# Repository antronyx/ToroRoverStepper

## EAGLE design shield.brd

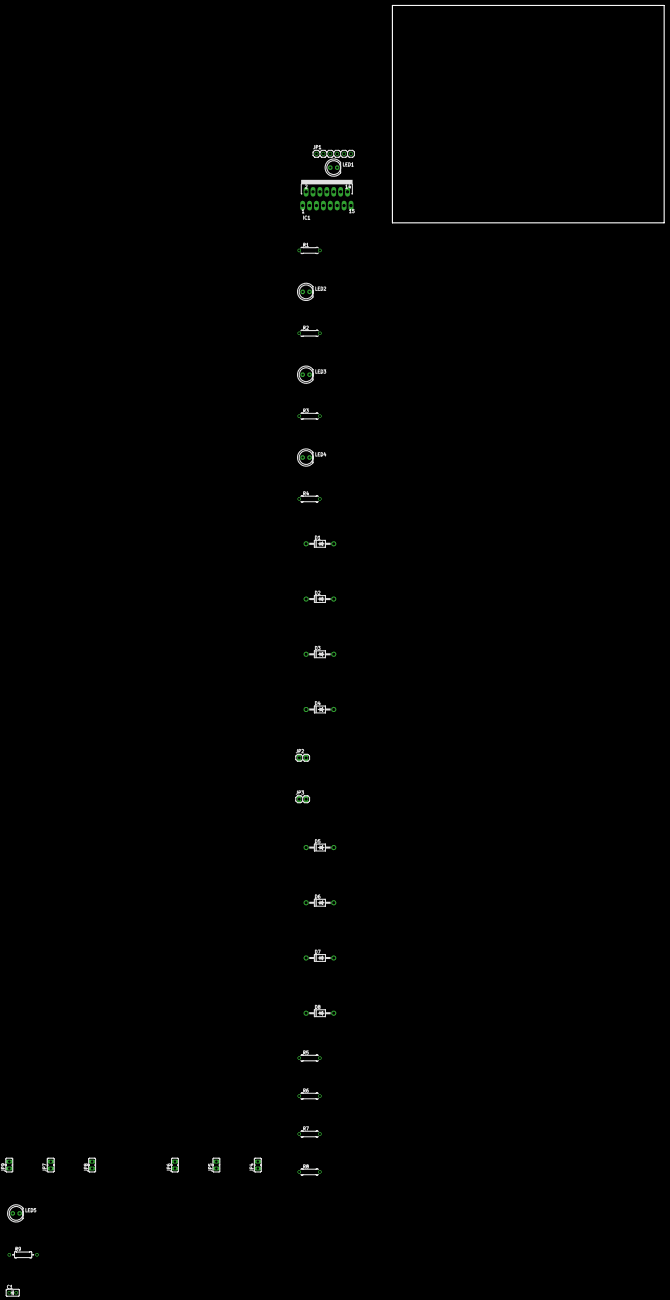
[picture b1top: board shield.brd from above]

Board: 2 copper layers, 100.0 x 80.0 mm, 33 parts (0 on the bottom side), 25 nets, no tracks yet.

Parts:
C1: C025-025X050
D1, D2, D3, D4, D5, D6, D7, D8: 1N4004; DO41-10
IC1: L298; MULTIWATT-15
JP1: 1X06
JP2, JP3: 1X02
JP4, JP5, JP6, JP7, JP8, JP9: JP1
LED1, LED2, LED3, LED4, LED5: LED5MM
R1, R2, R3, R4, R5, R6, R7, R8: 0207/7
R9: 0207/10

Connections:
+12V: D5.C, D6.C, D7.C, IC1.4
GND: D1.A, D2.A, D3.A, D4.A, IC1.8, JP7.2, JP9.2, R1.1
unnamed: IC1.6, JP1.6
unnamed: IC1.5, JP1.5, LED4.A, R8.1
unnamed: IC1.7, JP1.4, LED3.A, R7.1
unnamed: IC1.10, JP1.3, LED2.A, R6.1
unnamed: IC1.12, JP1.2, LED1.A, R5.1
unnamed: IC1.11, JP1.1
unnamed: LED1.K, R1.2
unnamed: LED2.K, R2.2
unnamed: LED3.K, R3.2
unnamed: LED4.K, R4.2
unnamed: D4.C, D8.A, IC1.14, JP2.2
unnamed: D3.C, D7.A, IC1.13, JP2.1
unnamed: D2.C, D6.A, IC1.3, JP3.2
unnamed: D1.C, D5.A, IC1.2, JP3.1
unnamed: JP4.1, R5.2
unnamed: JP5.1, R6.2
unnamed: JP6.1, R7.2
unnamed: JP8.1, R8.2
unnamed: IC1.1, JP7.1
unnamed: IC1.15, JP9.1
unnamed: LED5.K, R9.2
unnamed: C1.2, R9.1
VCC: IC1.9, JP4.2, JP5.2, JP6.2, JP8.2, LED5.A

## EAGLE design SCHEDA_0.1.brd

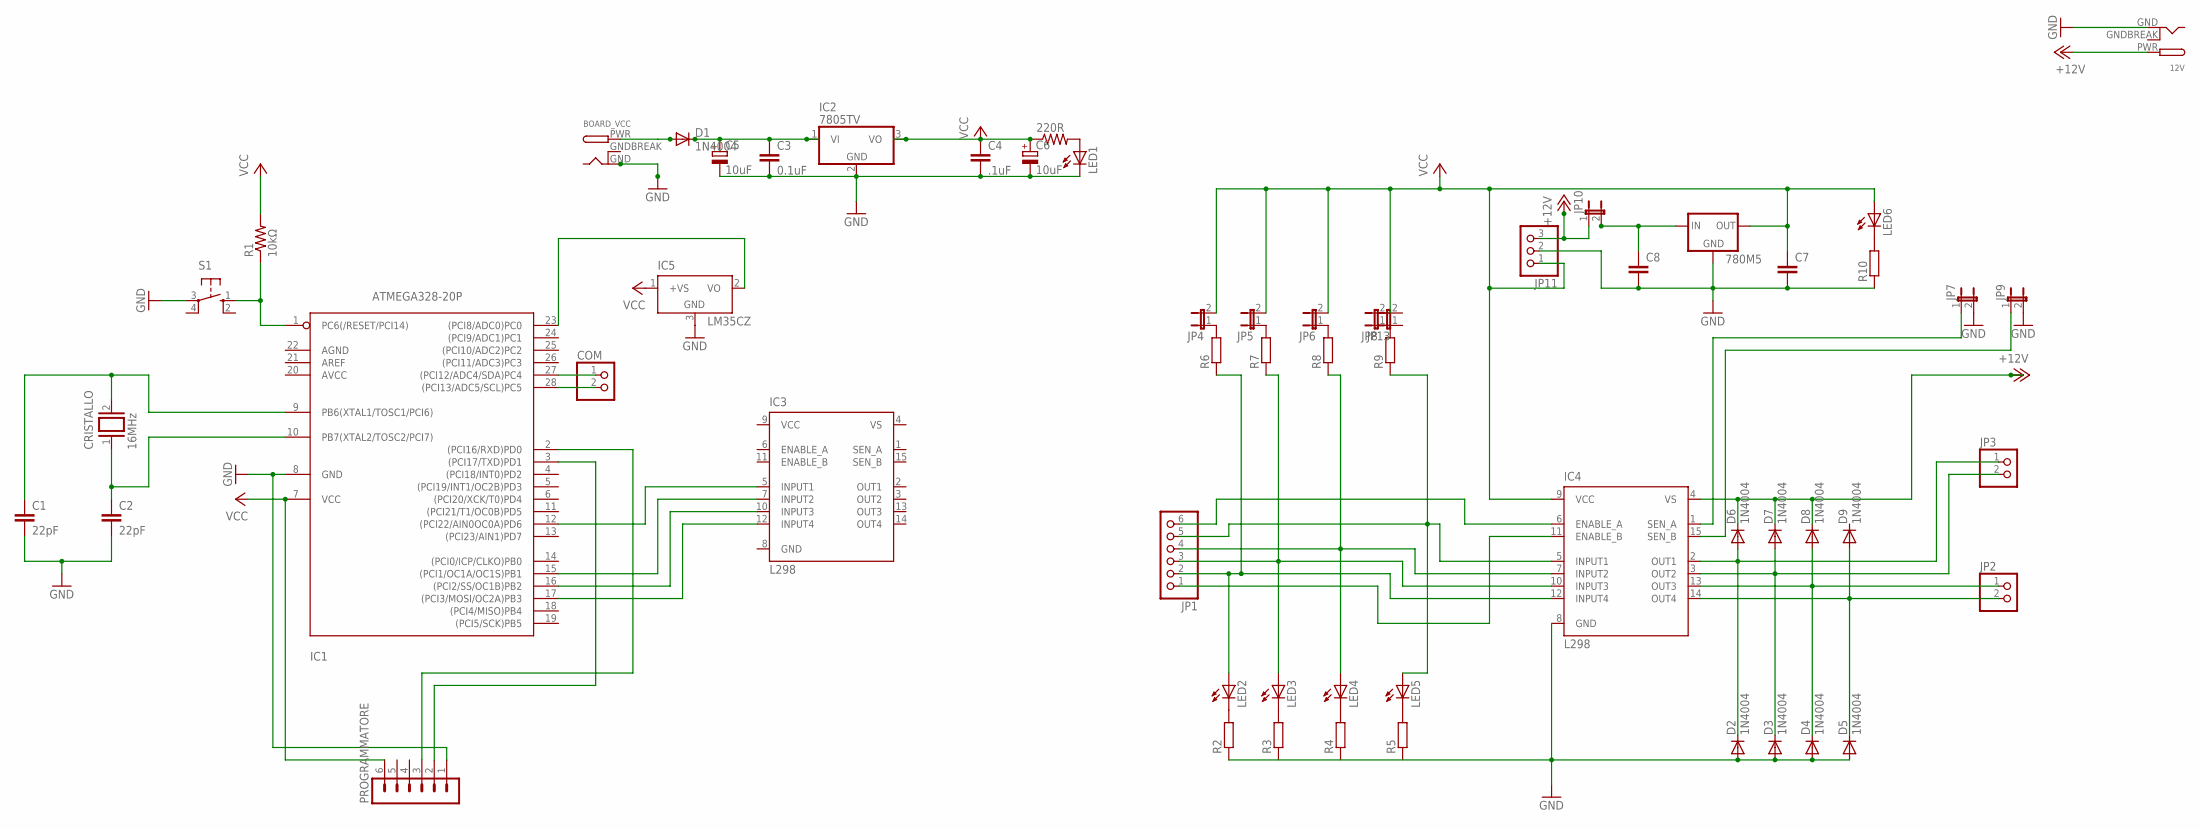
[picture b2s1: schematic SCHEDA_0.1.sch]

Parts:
12V: DCBARRELPTH; DCJACK_2MM_PTH
220R: R-US_0204/7; 0204/7
780M5: 78XXS
BOARD_VCC: DCBARRELPTH; DCJACK_2MM_PTH
C1, C2: 22pF; C5B3
C3: 0.1uF; C025-024X044
C4: .1uF; C025-024X044
C5, C6: 10uF; E1,8-4
C7, C8: C-EU025-025X050; C025-025X050
COM: PINHD-1X2; 1X02
CRISTALLO: 16MHz; QS
D1, D2, D3, D4, D5, D6, D7, D8, D9: 1N4004; DO41-10
IC1: ATMEGA328-20P; DIL28-3
IC2: 7805TV; TO220V
IC3, IC4: L298; MULTIWATT-15
IC5: LM35CZ; TO92
JP1: PINHD-1X6; 1X06
JP2, JP3: PINHD-1X2; 1X02
JP4, JP5, JP6, JP7, JP8, JP9, JP10, JP13: JP1E; JP1
JP11: PINHD-1X3; 1X03
LED1: LED3MM
LED2, LED3, LED4, LED5, LED6: LED5MM
PROGRAMMATORE: MA06-1
R1: 10kΩ; 0207/10
R2, R3, R4, R5, R6, R7, R8, R9: R-EU_0207/7; 0207/7
R10: R-EU_0207/10; 0207/10
S1: 40-XX; B3F-40XX

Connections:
+12V: D6.C, D7.C, D8.C, IC4.4 (VS), JP10.1, JP11.3
-: COM.1, IC1.27 ((PCI12/ADC4/SDA)PC4)
GND: 12V.GND, 780M5.GND, BOARD_VCC.GND, C1.2, C2.2, C3.2, C4.2, C5.-, C6.-, C7.2, C8.2, D2.A, D3.A, D4.A, D5.A, IC1.8 (GND), IC2.2 (GND), IC3.8 (GND), IC4.8 (GND), IC5.3 (GND), JP7.2, JP9.2, JP11.2, LED1.K (C), PROGRAMMATORE.1, R2.1, R10.1, S1.3
GNDBREAK: 12V.GNDBREAK, BOARD_VCC.GNDBREAK
unnamed: C1.1, CRISTALLO.2, IC1.9 (PB6(XTAL1/TOSC1/PCI6))
unnamed: C2.1, CRISTALLO.1, IC1.10 (PB7(XTAL2/TOSC2/PCI7))
unnamed: IC1.1 (PC6(/RESET/PCI14)), R1.1, S1.1 (S)
unnamed: IC1.15 ((PCI1/OC1A/OC1S)PB1), IC3.7 (INPUT2)
unnamed: IC1.3 ((PCI17/TXD)PD1), PROGRAMMATORE.2
unnamed: C3.1, C5.+, D1.C, IC2.1 (VI)
unnamed: IC1.2 ((PCI16/RXD)PD0), PROGRAMMATORE.3
unnamed: IC1.16 ((PCI2/SS/OC1B)PB2), IC3.10 (INPUT3)
unnamed: COM.2, IC1.28 ((PCI13/ADC5/SCL)PC5)
unnamed: IC1.17 ((PCI3/MOSI/OC2A)PB3), IC3.12 (INPUT4)
unnamed: IC1.12 ((PCI22/AIN0OC0A)PD6), IC3.5 (INPUT1)
unnamed: IC4.6 (ENABLE_A), JP1.6
unnamed: IC4.5 (INPUT1), JP1.5, LED5.A, R9.1
unnamed: IC4.7 (INPUT2), JP1.4, LED4.A, R8.1
unnamed: IC4.10 (INPUT3), JP1.3, LED3.A, R7.1
unnamed: IC4.12 (INPUT4), JP1.2, LED2.A, R6.1
unnamed: IC4.11 (ENABLE_B), JP1.1
unnamed: LED2.K (C), R2.2
unnamed: LED3.K (C), R3.2
unnamed: LED4.K (C), R4.2
unnamed: BOARD_VCC.PWR, D1.A
unnamed: LED5.K (C), R5.2
unnamed: 220R.2, LED1.A
unnamed: D5.C, D9.A, IC4.14 (OUT4), JP2.2
unnamed: D4.C, D8.A, IC4.13 (OUT3), JP2.1
unnamed: D3.C, D7.A, IC4.3 (OUT2), JP3.2
unnamed: D2.C, D6.A, IC4.2 (OUT1), JP3.1
unnamed: JP4.1, R6.2
unnamed: JP5.1, R7.2
unnamed: JP6.1, R8.2
unnamed: JP8.1, R9.2
unnamed: IC4.1 (SEN_A), JP7.1
unnamed: IC4.15 (SEN_B), JP9.1
unnamed: LED6.K (C), R10.2
unnamed: 780M5.IN, C8.1, JP10.2
unnamed: IC1.23 ((PCI8/ADC0)PC0), IC5.2 (VO)
VCC: 220R.1, 780M5.OUT, C4.1, C6.+, C7.1, IC1.7 (VCC), IC2.3 (VO), IC3.9 (VCC), IC4.9 (VCC), IC5.1 (+VS), JP4.2, JP5.2, JP6.2, JP8.2, JP11.1, LED6.A, PROGRAMMATORE.6, R1.2
VS: IC3.4 (VS)

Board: 2 copper layers, 58 parts (0 on the bottom side), 41 nets, no tracks yet.
